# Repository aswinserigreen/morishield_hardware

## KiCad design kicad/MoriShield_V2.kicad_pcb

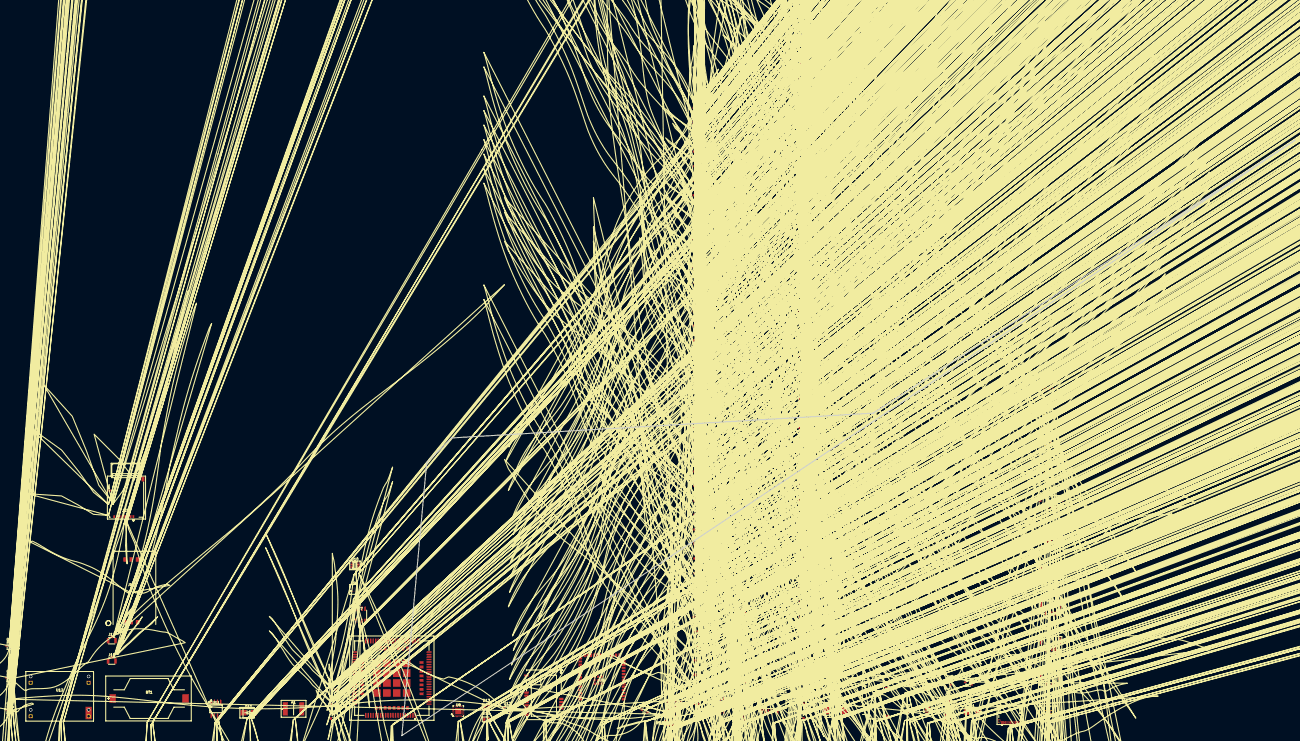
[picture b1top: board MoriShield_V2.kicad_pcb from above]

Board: 4 copper layers, 360.0 x 240.0 mm, 161 parts (0 on the bottom side), 92 nets, no tracks yet.

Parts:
BT1: SMTU2032-LF_BT1; SMTU2032-LF_131
C1: Generic Capacitor_100uF; Generic Capacitor_39
C1_1: Cap-0603-NO-V_C1; Cap-0603-NO-V_161
C2: Generic Capacitor_100uF; Generic Capacitor_125
C2_1: Cap-0603-NO-V_C2; Cap-0603-NO-V_160
C3: Generic Capacitor_47uF; Generic Capacitor_137
C3_1: Cap-0603-NO-V_C3; Cap-0603-NO-V_156
C4: Generic Capacitor_22uF; Generic Capacitor_42
C5: Generic Capacitor_10uF; Generic Capacitor_26
C6: Generic Capacitor_10uF; Generic Capacitor_104
C7: Generic Capacitor_1uF; Generic Capacitor_35
C8: Generic Capacitor_10uF; Generic Capacitor_3
C9: Generic Capacitor_100nF; Generic Capacitor_14
C10: Generic Capacitor_100nF; Generic Capacitor_52
C11: Generic Capacitor_100nF; Generic Capacitor_69
C12: Generic Capacitor_100nF; Generic Capacitor_44
C13: Generic Capacitor_100nF; Generic Capacitor_37
C14: Generic Capacitor_100nF; Generic Capacitor_92
C15: Generic Capacitor_100nF; Generic Capacitor_38
C16: Generic Capacitor_4.7uF; Generic Capacitor_98
C17: Generic Capacitor_100nF; Generic Capacitor_62
C18: Generic Capacitor_100nF; Generic Capacitor_106
C19: Generic Capacitor_22uF; Generic Capacitor_126
C20: Generic Capacitor_1uF; Generic Capacitor_77
C21: Generic Capacitor_22uF; Generic Capacitor_113
C22: Generic Capacitor_22uF; Generic Capacitor_24
C23: Generic Capacitor_10uF; Generic Capacitor_110
C24: Generic Capacitor_10uF; Generic Capacitor_144
C25: Generic Capacitor_47uF; Generic Capacitor_15
C26: Generic Capacitor_47uF; Generic Capacitor_57
C27: Generic Capacitor_10nF; Generic Capacitor_64
C28: Generic Capacitor_1nF; Generic Capacitor_79
C29: Generic Capacitor_47pF; Generic Capacitor_112
C30: Generic Capacitor_100nF; Generic Capacitor_56
C31: Generic Capacitor_100nF; Generic Capacitor_21
C32: Generic Capacitor_1uF; Generic Capacitor_22
C35: Generic Capacitor_100nF; Generic Capacitor_58
C36: Generic Capacitor_10uF; Generic Capacitor_132
C37: Generic Capacitor_100nF; Generic Capacitor_36
C38: Generic Capacitor_100nF; Generic Capacitor_93
C39: Generic Capacitor_1uF; Generic Capacitor_146
C40: Generic Capacitor_1uF; Generic Capacitor_118
C41: Generic Capacitor_100nF; Generic Capacitor_130
C42: Generic Capacitor_10uF; Generic Capacitor_47
C43: Generic Capacitor_100nF; Generic Capacitor_150
C44: Generic Capacitor_0pF; Generic Capacitor_123
C45: Generic Capacitor_0pF; Generic Capacitor_95
D1: SMBJ33A_D1; SMBJ33A_117
D2: USBLC6-2SC6_D2; USBLC6-2SC6_140
D3: USBLC6-2SC6_D3; USBLC6-2SC6_66
D4: USBLC6-2SC6_D4; USBLC6-2SC6_33
D5: USBLC6-2SC6_D5; USBLC6-2SC6_54
D6: USBLC6-2SC6_D6; USBLC6-2SC6_41
D7: USBLC6-2SC6_D7; USBLC6-2SC6_99
D8: USBLC6-2SC6_D8; USBLC6-2SC6_40
D9: SM712_D9; SM712_149
D10: 1N4148WS-13-F_D10; 1N4148WS-13-F_23
D11: SS54B_D11; SS54B_85
D12: APT2012SURCK_D12; APT2012SURCK_138
D13: APT2012SURCK_D13; APT2012SURCK_53
D14: ESDA6V1BC6_D14; ESDA6V1BC6_121
D15: SS54_D15; SS54_133
D16: 1N4148WS-13-F_D16; 1N4148WS-13-F_88
F1: SMDC300F/24-2_F1; SMDC300F/24-2_71
IC1: MPU-6500_IC1; MPU-6500_155
J1: B2B-XH-A(LF)(SN)_J1; B2B-XH-A(LF)(SN)_116
J2: BM04B-GHS-TBT(LF)(SN)_J2; BM04B-GHS-TBT(LF)(SN)_76
J3: BM04B-GHS-TBT(LF)(SN)_J3; BM04B-GHS-TBT(LF)(SN)_12
J4: BM04B-GHS-TBT(LF)(SN)_J4; BM04B-GHS-TBT(LF)(SN)_20
J5: BM05B-GHS-TBT(LF)(SN)(N)_J5; BM05B-GHS-TBT(LF)(SN)(N)_11
J6: BM05B-GHS-TBT(LF)(SN)(N)_J6; BM05B-GHS-TBT(LF)(SN)(N)_59
J7: BM05B-GHS-TBT(LF)(SN)(N)_J7; BM05B-GHS-TBT(LF)(SN)(N)_124
J8: B2B-XH-A(LF)(SN)_J8; B2B-XH-A(LF)(SN)_97
J9: B2B-XH-A(LF)(SN)_J9; B2B-XH-A(LF)(SN)_119
J10: B2B-XH-A(LF)(SN)_J10; B2B-XH-A(LF)(SN)_46
J11: U.FL-R-SMT-1_J11; U.FL-R-SMT-1_135
J12: U.FL-R-SMT-1_J12; U.FL-R-SMT-1_27
J13: USB4215-03-A_J13; USB4215-03-A_114
J14: 7111S2015X02LF_J14; 7111S2015X02LF_78
J15: DM3AT-SF-PEJM5_J15; DM3AT-SF-PEJM5_32
J16: B2B-XH-A(LF)(SN)_J16; B2B-XH-A(LF)(SN)_148
L1: Generic Inductor_1nH; Generic Inductor_134
L2: Generic Inductor_4.7uH; Generic Inductor_153
L3: Generic Inductor_4.7uH; Generic Inductor_105
Q1: AO3400A_Q1; AO3400A_10
Q2: AO3400A_Q2; AO3400A_111
Q3: AO3400A_Q3; AO3400A_89
Q4: MMBT3904LT3G_Q4; MMBT3904LT3G_65
Q5: AO3401A_Q5; AO3401A_120
Q6: MMBT3904LT3G_Q6; MMBT3904LT3G_8
Q7: MMBT3904LT3G_Q7; MMBT3904LT3G_72
R1: Generic Resistor_220Ω; Generic Resistor_122
R1_1: Res-0603-US-Template_10K; Res-0603-US-Template_159
R2: Generic Resistor_220Ω; Generic Resistor_29
R2_1: Res-0603-US-Template_10K; Res-0603-US-Template_163
R3: Generic Resistor_220Ω; Generic Resistor_147
R3_1: Res-0603-US-Template_10K; Res-0603-US-Template_157
R4: Generic Resistor_10kΩ; Generic Resistor_34
R4_1: Res-0603-US-Template_10K; Res-0603-US-Template_158
R5: Generic Resistor_10kΩ; Generic Resistor_61
R5_1: Res-0603-US-Template_10K; Res-0603-US-Template_162
R6: Generic Resistor_10kΩ; Generic Resistor_152
R7: Generic Resistor_4.7kΩ; Generic Resistor_18
R8: Generic Resistor_4.7kΩ; Generic Resistor_49
R9: Generic Resistor_2.2kΩ; Generic Resistor_25
R10: Generic Resistor_2.2kΩ; Generic Resistor_145
R11: Generic Resistor_4.7kΩ; Generic Resistor_136
R12: Generic Resistor_4.7kΩ; Generic Resistor_73
R13: Generic Resistor_10kΩ; Generic Resistor_19
R14: Generic Resistor_10kΩ; Generic Resistor_50
R15: Generic Resistor_10kΩ; Generic Resistor_30
R16: Generic Resistor_1kΩ; Generic Resistor_43
R17: Generic Resistor_10kΩ; Generic Resistor_86
R18: Generic Resistor_22Ω; Generic Resistor_141
R19: Generic Resistor_22Ω; Generic Resistor_28
R20: Generic Resistor_22Ω; Generic Resistor_94
R21: Generic Resistor_22Ω; Generic Resistor_154
R22: Generic Resistor_10kΩ; Generic Resistor_100
R23: Generic Resistor_10kΩ; Generic Resistor_107
R24: Generic Resistor_120Ω; Generic Resistor_17
R25: Generic Resistor_10Ω; Generic Resistor_139
R26: Generic Resistor_10Ω; Generic Resistor_74
R27: Generic Resistor_5.1kΩ; Generic Resistor_90
R28: Generic Resistor_5.1kΩ; Generic Resistor_96
R29: Generic Resistor_1kΩ; Generic Resistor_45
R30: Generic Resistor_1kΩ; Generic Resistor_4
R31: Generic Resistor_0Ω; Generic Resistor_70
R32: Generic Resistor_0Ω; Generic Resistor_60
R33: Generic Resistor_0Ω; Generic Resistor_16
R34: Generic Resistor_0Ω; Generic Resistor_63
R35: Generic Resistor_0Ω; Generic Resistor_48
R36: Generic Resistor_10kΩ; Generic Resistor_55
R37: Generic Resistor_10kΩ; Generic Resistor_83
R38: Generic Resistor_100kΩ; Generic Resistor_75
R39: Generic Resistor_100kΩ; Generic Resistor_13
R40: Generic Resistor_1kΩ; Generic Resistor_129
R41: Generic Resistor_1kΩ; Generic Resistor_6
R42: Generic Resistor_10kΩ; Generic Resistor_109
R43: Generic Resistor_40.2kΩ; Generic Resistor_115
R44: Generic Resistor_12.7kΩ; Generic Resistor_68
R45: Generic Resistor_33kΩ; Generic Resistor_87
R46: Generic Resistor_37.4kΩ; Generic Resistor_91
R47: Generic Resistor_10kΩ; Generic Resistor_151
R48: Generic Resistor_29.4kΩ; Generic Resistor_51
R49: Generic Resistor_10kΩ; Generic Resistor_102
R50: Generic Resistor_0Ω; Generic Resistor_103
SW1: 1571563-8_SW1; 1571563-8_108
SW2: 1571563-8_SW2; 1571563-8_128
U1: ESP32-S3-WROOM-1-N16R8_U1; ESP32-S3-WROOM-1-N16R8_9
U2: E22-900M22S_U2; E22-900M22S_84
U3: SIM7600G-H_R2_U3; SIM7600G-H_R2_5
U4: FDC1004DSCJ_U4; FDC1004DSCJ_82
U6: DS3231S#T&R_U6; DS3231S#T&R_7
U7: MAX3485ESA+_U7; MAX3485ESA+_31
U8: CP2102N-A02-GQFN24_U8; CP2102N-A02-GQFN24_143
U9: TXU0202DTTR_U9; TXU0202DTTR_81
U10: MP2315SGJ-P_U10; MP2315SGJ-P_67
U11: TPS54331D_U11; TPS54331D_101
U12: DC-DC Multi-output Buck Converter (3.3V/5V/9V/12V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; DC-DC Multi-output Buck Converter (3.3V/5V/9V/12V)_80
U13: AP2127K-1.8TRG1_U13; AP2127K-1.8TRG1_127
U14: AP2152SG-13_U14; AP2152SG-13_142

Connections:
1V8_RAIL: C17.P1, C40.P1, U9.OE, U9.VCCA, U13.VOUT
3V3_RAIL: C4.P1, C5.P1, C6.P1, C7.P1, C8.P1, C9.P1, C10.P1, C11.P1, C12.P1, C13.P1, C14.P1, C15.P1, C16.P1, C18.P1, C21.P1, C22.P1, C39.P1, C42.P1, C43.P1, D3.VBUS, D4.VBUS, D5.VBUS, D6.VBUS, D7.VBUS, D8.VBUS, J2.1, J3.1, J4.1, J7.1, J15.VDD, L2.P2, R7.P1, R8.P1, R9.P1, R10.P1, R11.P1, R12.P1, R13.P1, R14.P1, R15.P1, R23.P1, R30.P1, R36.P1, R37.P1, R42.P1, R43.P1, R49.P1, U1.3V3, U2.VCC, U4.VDD, U6.VCC, U7.VCC, U8.VDD, U8.VIO, U8.VREGIN, U9.VCCB, U13.VIN, U13.~{SHUTDOWN}
3V8_PRE_FILTER: C25.P1, C26.P1, L1.P1, L3.P2, R46.P1
3V8_SIM_RAIL: C1.P1, C30.P1, L1.P2
5V_RAIL: C3.P1, C19.P1, C23.P1, C24.P1, D15.K, J5.1, R38.P1, R39.P1, U10.IN, U11.VIN, U12.+ OUT
12V_IN: D1.C, F1.P1, J1.1
12V_PROTECTED: F1.P2, Q5.D
12V_RAIL: C2.P1, D10.2, J8.1, J9.1, J10.1, Q5.S, U12.+ IN
AUTO_DTR_B: Q6.B, R40.P2
AUTO_RTS_B: Q7.B, R41.P2
BOOT_BTN: Q7.C, R13.P2, SW1.~, U1.IO0
BUZZ_GATE: R3.P1, U1.IO38
BUZZ_GATE_DRV: Q3.G, R3.P2, R6.P1
BUZZ_SW: D10.1, J10.2, Q3.D
CP2102_RST: C41.P1, R42.P2, U8.RSTb
DIO2: U2.DIO2, U2.TXEN
DTR: Q7.E, R40.P1, U8.DTR
EN: C32.P1, Q6.C, R15.P2, SW2.~, U1.EN
FDC_CIN1: J6.1, U4.CIN1
FDC_CIN2: J6.2, U4.CIN2
FDC_SHLD1: J6.3, U4.SHLD1
FDC_SHLD2: J6.4, U4.SHLD2
GND: BT1.-, C1.P2, C1_1.P2, C2.P2, C2_1.P2, C3.P2, C3_1.P2, C4.P2, C5.P2, C6.P2, C7.P2, C8.P2, C9.P2, C10.P2, C11.P2, C12.P2, C13.P2, C14.P2, C15.P2, C16.P2, C17.P2, C18.P2, C19.P2, C20.P2, C21.P2, C22.P2, C23.P2, C24.P2, C25.P2, C26.P2, C27.P2, C28.P2, C29.P2, C30.P2, C32.P2, C35.P2, C36.P2, C39.P2, C40.P2, C41.P2, C42.P2, C43.P2, D1.A, D2.GND, D3.GND, D4.GND, D5.GND, D6.GND, D7.GND, D8.GND, D9.3, D11.A, D12.K, IC1.GND, J1.2, J2.2, J3.2, J4.2, J5.2, J6.5, J7.2, J11.2, J11.3, J13.GND_A, J13.GND_B, J13.SHIELD, J15.SHIELD, J15.VSS, Q1.S, Q2.S, Q3.S, Q5.G, R1_1.P2, R2_1.P2, R4.P2, R5.P2, R6.P2, R27.P2, R28.P2, R44.P2, R47.P2, U1.GND_1, U1.GND_2, U1.GND_3, U1.GND_4, U1.GND_5, U1.GND_6, U1.GND_7, U1.GND_8, U1.GND_9, U1.GND_10, U1.GND_11, U4.EP, U4.GND, U6.GND, U7.GND, U8.EP, U8.GND, U9.GND, U10.AAM, U10.GND, U11.GND, U12.- IN, U12.- OUT, U13.GND, U14.GND
GPIO3_STRAP: R14.P2, U1.IO3
I2C1_SCL: D3.I/O2, D4.I/O2, J2.4, J3.4, R8.P2, U1.IO9, U6.SCL
I2C1_SDA: D3.I/O1, D4.I/O1, J2.3, J3.3, R7.P2, U1.IO8, U6.SDA
I2C2_SCL: D5.I/O2, J4.4, R10.P2, U1.IO18, U4.SCL
I2C2_SDA: D5.I/O1, J4.3, R9.P2, U1.IO17, U4.SDA
I2C3_SCL: D6.I/O2, J7.5, R12.P2, U1.IO6
I2C3_SDA: D6.I/O1, J7.4, R11.P2, U1.IO5
LED_GREEN_GATE: R1.P1, U1.IO2
LED_GREEN_GATE_DRV: Q1.G, R1.P2, R4.P1
LED_GREEN_SW: J8.2, Q1.D
LED_RED_GATE: R2.P1, U1.IO4
LED_RED_GATE_DRV: Q2.G, R2.P2, R5.P1
LED_RED_SW: J9.2, Q2.D
LORA_ANT: J11.1, U2.ANT
LORA_BUSY: U1.IO7, U2.BUSY
LORA_DIO1: U1.IO14, U2.DIO1
LORA_NRST: R36.P2, U1.IO21, U2.NRST
LORA_NSS: U1.IO10, U2.NSS
Net 1: C1_1.P1, IC1.REGOUT
Net 2: IC1.SDO/ADO, R1_1.P1
Net 4: IC1.FSYNC, R2_1.P1
Net 6: C2_1.P1, C3_1.P1, IC1.VDD, IC1.VDDIO, R3_1.P2, R4_1.P2, R5_1.P2
Net 8: IC1.nCS, R3_1.P1
Net 9: IC1.SCL/SCLK, R4_1.P1
Net 10: IC1.SDA/SDI, R5_1.P1
PWR_LED_A: D12.A, R30.P2
RS485_A: D9.1, J16.1, R24.P1, R25.P2
RS485_A_IC: R25.P1, U7.A
RS485_B: D9.2, J16.2, R24.P2, R26.P2
RS485_B_IC: R26.P1, U7.B
RS485_DE_RE: U1.IO41, U7.DE, U7.~{RE}
RTC_RST: R37.P2, U6.RST
RTC_VBAT: BT1.+, U6.VBAT
RTS: Q6.E, R41.P1, U8.RTS
SD_CS: J15.CD/DAT3, R49.P2, U1.IO47
SPI_MISO: J15.DAT0, U1.IO13, U2.MISO
SPI_MOSI: J15.CMD, R18.P2, U2.MOSI
SPI_MOSI_MCU: R18.P1, U1.IO11
SPI_SCK: J15.CLK, R19.P2, U2.SCK
SPI_SCK_MCU: R19.P1, U1.IO12
U10_BST: C37.P1, D16.2, U10.BST
U10_EN: R38.P2, U10.EN
U10_FB: R43.P2, R44.P1, U10.FB
U10_SW: C37.P2, L2.P1, U10.SW
U10_VCC: C20.P1, D16.1, U10.VCC
U11_BOOT: C38.P1, U11.BOOT
U11_COMP: C29.P1, R48.P1, U11.COMP
U11_COMP_RC: C28.P1, R48.P2
U11_EN: R39.P2, U11.EN
U11_FB: R46.P2, R47.P1, U11.VSENSE
U11_PH: C38.P2, D11.K, L3.P1, U11.PH
U11_SS: C27.P1, U11.SS
UART0_RX: U1.RXD0, U8.TXD
UART0_TX: U1.TXD0, U8.RXD
UART1_RX: D7.I/O2, J5.4, U1.IO16
UART1_TX: D7.I/O1, J5.3, U1.IO15
UART2_RX: R32.P1, R35.P1, U1.IO39
UART2_RX_485: R35.P2, U7.RO
UART2_TX: R31.P1, R34.P1, U1.IO40
UART2_TX_485: R34.P2, U7.DI
USB_CC1: J13.CC1, R27.P1
USB_CC2: J13.CC2, R28.P1
USB_DEBUG_5V: D15.A, U14.OUT1, U14.OUT2
USB_DN: D2.I/O2, U8.D-
USB_DN_CONN: J13.DN1, J13.DN2
USB_DP: D2.I/O1, U8.D+
USB_DP_CONN: J13.DP1, J13.DP2
USB_VBUS: C35.P1, C36.P1, D2.VBUS, J13.VBUS_A, J13.VBUS_B, U8.VBUS, U14.EN1, U14.EN2, U14.IN
WIND_SPEED: D8.I/O1, J7.3, R23.P2, U1.IO42

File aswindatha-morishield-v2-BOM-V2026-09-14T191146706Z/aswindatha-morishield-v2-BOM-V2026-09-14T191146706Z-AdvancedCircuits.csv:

Component Description,QTY,Ref Des,Mfg P/N #,Manufacturer,Distributor P/N #
"Connector","1","BT1","SMTU2032-LF","Renata",""
"Non-Polarized Capacitor, 100uF, SMD_0603_1608Metric","2","C1,C2","","",""
"Non-Polarized Capacitor","3","C1,C2,C3","","",""
"Non-Polarized Capacitor, 100nF, SMD_0603_1608Metric","16","C10,C11,C12,C13,C14,C15,C17,C18,C30,C31,C35,C37,C38,C41,C43,C9","","",""
"Non-Polarized Capacitor, 4.7uF, SMD_0603_1608Metric","1","C16","","",""
"Non-Polarized Capacitor, 22uF, SMD_0603_1608Metric","4","C19,C21,C22,C4","","",""
"Non-Polarized Capacitor, 1uF, SMD_0603_1608Metric","5","C20,C32,C39,C40,C7","","",""
"Non-Polarized Capacitor, 10uF, SMD_0603_1608Metric","7","C23,C24,C36,C42,C5,C6,C8","","",""
"Non-Polarized Capacitor, 47uF, SMD_0603_1608Metric","3","C25,C26,C3","","",""
"Non-Polarized Capacitor, 10nF, SMD_0603_1608Metric","1","C27","","",""
"Non-Polarized Capacitor, 1nF, SMD_0603_1608Metric","1","C28","","",""
"Non-Polarized Capacitor, 47pF, SMD_0603_1608Metric","1","C29","","",""
"Non-Polarized Capacitor, 0pF, SMD_0603_1608Metric","2","C44,C45","","",""
"TVS, SMB_L4.6-W3.6-LS5.3-RD","1","D1","SMBJ33A","SHIKUES(时科)",""
"Protection","7","D2,D3,D4,D5,D6,D7,D8","USBLC6-2SC6","STMicroelectronics",""
"TVS, SOT-23-3_L2.9-W1.6-P1.90-LS2.8-BR","1","D9","SM712","MDD",""
"Switching Diode, SOD-323_L1.8-W1.3-LS2.5-RD","2","D10,D16","1N4148WS-13-F","DIODES(美台)",""
"Diode","1","D11","SS54B","MDD",""
"LED","2","D12,D13","APT2012SURCK","Kingbright",""
"Protection","1","D14","ESDA6V1BC6","STMicroelectronics",""
"Schottky Barrier Diodes (SBD), SMC_L6.9-W5.9-LS7.9-RD","1","D15","SS54","MDD(Microdiode Semiconductor)",""
"Fuse","1","F1","SMDC300F/24-2","Littelfuse Inc.",""
"IMU","1","IC1","MPU-6500","TDK InvenSense",""
"Wire To Board / Wire To Wire Connector, CONN-TH_B2B-XH-A-LF-SN","5","J1,J10,J16,J8,J9","B2B-XH-A(LF)(SN)","JST",""
"Wire To Board / Wire To Wire Connector, CONN-SMD_4P-P1.25_BM04B-GHS-TBT-LF-SN","3","J2,J3,J4","BM04B-GHS-TBT(LF)(SN)","JST",""
"Wire To Board / Wire To Wire Connector, CONN-SMD_BM05B-GHS-TBT","3","J5,J6,J7","BM05B-GHS-TBT(LF)(SN)(N)","JST",""
"Connector","2","J11,J12","U.FL-R-SMT-1","Hirose Electric Co Ltd",""
"USB C, GCT_USB4215-03-A_REVA","1","J13","USB4215-03-A","GCT",""
"Connector","1","J14","7111S2015X02LF","Amphenol ICC
",""
"Connector","1","J15","DM3AT-SF-PEJM5","Hirose Electric Co Ltd",""
"Inductor, 1nH, SMD_0603_1608Metric","1","L1","","",""
"Inductor, 4.7uH, SMD_0603_1608Metric","2","L2,L3","","",""
"Transistor","3","Q1,Q2,Q3","AO3400A","Alpha & Omega Semiconductor Inc.",""
"Bipolar Transistors - BJT, SOT-23-3_L2.9-W1.3-P1.90-LS2.4-BR","3","Q4,Q6,Q7","MMBT3904LT3G","onsemi(安森美)",""
"MOSFETs, SOT-23_L2.9-W1.3-P1.90-LS2.4-BR","1","Q5","AO3401A","UMW(友台半导体)",""
"Resistor, 220Ω, SMD_0603_1608Metric","3","R1,R2,R3","","",""
"Resistor, 10KΩ","5","R1,R2,R3,R4,R5","","",""
"Resistor, 2.2kΩ, SMD_0603_1608Metric","2","R10,R9","","",""
"Resistor, 4.7kΩ, SMD_0603_1608Metric","4","R11,R12,R7,R8","","",""
"Resistor, 10kΩ, SMD_0603_1608Metric","14","R13,R14,R15,R17,R22,R23,R36,R37,R4,R42,R47,R49,R5,R6","","",""
"Resistor, 1kΩ, SMD_0603_1608Metric","5","R16,R29,R30,R40,R41","","",""
"Resistor, 22Ω, SMD_0603_1608Metric","4","R18,R19,R20,R21","","",""
"Resistor, 120Ω, SMD_0603_1608Metric","1","R24","","",""
"Resistor, 10Ω, SMD_0603_1608Metric","2","R25,R26","","",""
"Resistor, 5.1kΩ, SMD_0603_1608Metric","2","R27,R28","","",""
"Resistor, 0Ω, SMD_0603_1608Metric","6","R31,R32,R33,R34,R35,R50","","",""
"Resistor, 100kΩ, SMD_0603_1608Metric","2","R38,R39","","",""
"Resistor, 40.2kΩ, SMD_0603_1608Metric","1","R43","","",""
"Resistor, 12.7kΩ, SMD_0603_1608Metric","1","R44","","",""
"Resistor, 33kΩ, SMD_0603_1608Metric","1","R45","","",""
"Resistor, 37.4kΩ, SMD_0603_1608Metric","1","R46","","",""
"Resistor, 29.4kΩ, SMD_0603_1608Metric","1","R48","","",""
"Switch","2","SW1,SW2","1571563-8","TE Connectivity ALCOSWITCH Switches",""
"Module","1","U1","ESP32-S3-WROOM-1-N16R8","Espressif Systems",""
"LoRa Modules, WIRELM-SMD_E22-900M22S","1","U2","E22-900M22S","EBYTE(亿佰特)",""
"Integrated Circuit, SIM7600GHR2","1","U3","SIM7600G-H R2","SIMCOM",""
"Touch Sensors, WSON-10_L3.0-W3.0-P0.50-LS3.0-BL-EP","1","U4","FDC1004DSCJ","TI(德州仪器)",""
"Real-time Clocks (RTC), SOIC-16_L10.3-W7.5-P1.27-LS10.3-BL","1","U6","DS3231S#T&R","ADI(亚德诺)/MAXIM(美信)",""
"Integrated Circuit, SO-8_L4.9-W3.9-P1.27-LS6.0-BL","1","U7","MAX3485ESA+","MAXIM(美信)",""
"Interface - Controllers, QFN-24_L4.0-W4.0-P0.50-TL-EP2.5","1","U8","CP2102N-A02-GQFN24","SILICON LABS",""
"Integrated Circuit","1","U9","TXU0202DTTR","Texas Instruments",""
"Integrated Circuit","1","U10","MP2315SGJ-P","Monolithic Power Systems Inc.",""
"DC-DC Converters, SOIC-8_L4.9-W3.9-P1.27-LS6.0-BL","1","U11","TPS54331D","TI(德州仪器)",""
"Buck Converter","1","U12","","DFRobot",""
"Linear Voltage Regulators (LDO), SOT-23-5_L3.0-W1.7-P0.95-LS2.8-BR","1","U13","AP2127K-1.8TRG1","DIODES(美台)",""
"Power Distribution Switches, SOIC-8_L4.9-W3.9-P1.27-LS6.0-BL","1","U14","AP2152SG-13","DIODES(美台)",""
